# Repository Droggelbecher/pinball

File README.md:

Repository with code & electronics documentation for my personal pinball project.

This is far from a complete documentation that by itself woul be sufficient to replicate this project,
nevertheless it might be useful to some.

*boards* contains source code & notes on electronics for the various circuit boards used in the machine.
The main game logic is in the the control module which is basically a Raspberry Pi (plus some level-shifting electronics).
*common_software* contains some bits and pieces of code common to different modules,
mostly around inter-module communication (eg. checksum computation)

Checkout [http://leetless.de]() for more information.

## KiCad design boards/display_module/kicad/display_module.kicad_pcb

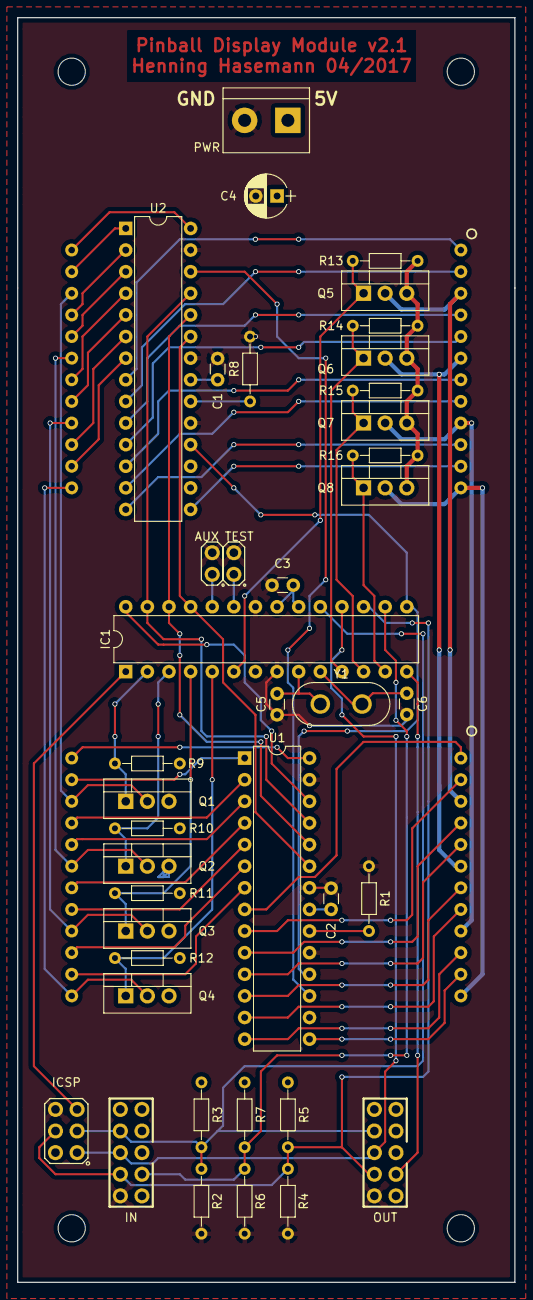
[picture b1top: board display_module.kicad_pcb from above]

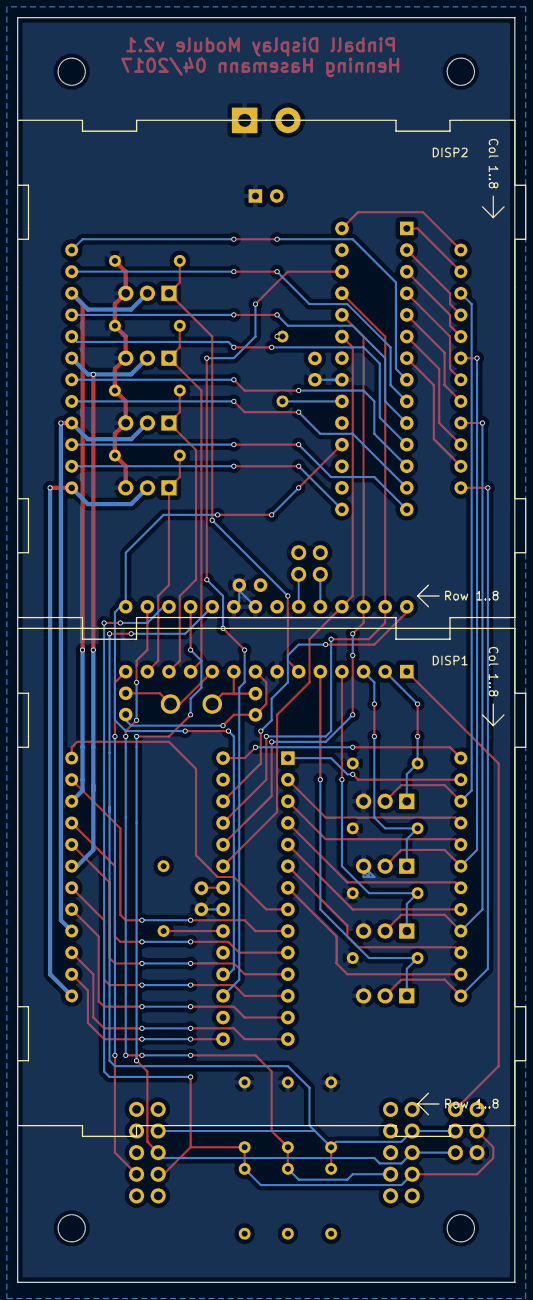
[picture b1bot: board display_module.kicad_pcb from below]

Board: 2 copper layers, 58.4 x 148.6 mm, 42 parts (2 on the bottom side), 68 nets.

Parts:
AUX: AUX; PINS1x2
C1, C2, C3: 100n; C_Disc_D3.0mm_W1.6mm_P2.50mm
C4: 10uF; CP_Radial_D5.0mm_P2.50mm
C5, C6: 22p; C_Disc_D3.0mm_W1.6mm_P2.50mm
DISP1, DISP2: LM23088A
IC1: ATMEGA328-P; DIP-28_W7.62mm
ICSP: ICSP; PINS3x2
IN: SW10
OUT: SW10
PWR: POWER; bornier2
Q1, Q2, Q3, Q4, Q5, Q6, Q7, Q8: NDP6020P; TO-220_Vertical
R1, R2, R4, R6, R8: 380; R_Axial_DIN0204_L3.6mm_D1.6mm_P7.62mm_Horizontal
R3, R5, R7: 190; R_Axial_DIN0204_L3.6mm_D1.6mm_P7.62mm_Horizontal
R9, R10, R11, R12, R13, R14, R15, R16: 10k; R_Axial_DIN0204_L3.6mm_D1.6mm_P7.62mm_Horizontal
TEST: TEST; PINS1x2
U1, U2: TLC5940NT; DIP-28_W7.62mm
Y1: 16M; Crystal_HC50_Vertical

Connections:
GND: AUX.2, C1.2, C2.2, C3.2, C4.2, C5.1, C6.2, IC1.8, IC1.22, ICSP.6, IN.5, OUT.5, PWR.2, R1.2, R2.2, R4.2, R6.2, R8.2, TEST.2, U1.19, U1.22, U1.27, U2.19, U2.22, U2.27
unnamed: C5.2, IC1.9, Y1.1
unnamed: C6.1, IC1.10, Y1.2
unnamed: DISP1.1, U1.8
unnamed: DISP1.2, U1.9
unnamed: DISP1.3, DISP2.3, Q5.2
unnamed: DISP1.4, U1.10
unnamed: DISP1.5, U1.11
unnamed: DISP1.6, DISP2.6, Q6.2
unnamed: DISP1.7, U1.12
unnamed: DISP1.8, U1.13
unnamed: DISP1.9, DISP2.9, Q7.2
unnamed: DISP1.10, U1.14
unnamed: DISP1.11, U1.15
unnamed: DISP1.12, DISP2.12, Q8.2
unnamed: DISP1.13, DISP2.13, Q4.2
unnamed: DISP1.14, U1.7
unnamed: DISP1.15, U1.6
unnamed: DISP1.16, DISP2.16, Q3.2
unnamed: DISP1.17, U1.5
unnamed: DISP1.18, U1.4
unnamed: DISP1.19, DISP2.19, Q2.2
unnamed: DISP1.20, U1.3
unnamed: DISP1.21, U1.2
unnamed: DISP1.22, DISP2.22, Q1.2
unnamed: DISP1.23, U1.1
unnamed: DISP1.24, U1.28
unnamed: DISP2.1, U2.8
unnamed: DISP2.2, U2.9
unnamed: DISP2.4, U2.10
unnamed: DISP2.5, U2.11
unnamed: DISP2.7, U2.12
unnamed: DISP2.8, U2.13
unnamed: DISP2.10, U2.14
unnamed: DISP2.11, U2.15
unnamed: DISP2.14, U2.7
unnamed: DISP2.15, U2.6
unnamed: DISP2.17, U2.5
unnamed: DISP2.18, U2.4
unnamed: DISP2.20, U2.3
unnamed: DISP2.21, U2.2
unnamed: DISP2.23, U2.1
unnamed: DISP2.24, U2.28
unnamed: IC1.1, ICSP.5
unnamed: IC1.2, Q1.1, R9.2
unnamed: IC1.3, Q2.1, R10.2
unnamed: IC1.4, Q3.1, R11.2
unnamed: IC1.5, Q4.1, R12.2
unnamed: IC1.6, Q5.1, R13.2
unnamed: IC1.11, Q6.1, R14.2
unnamed: IC1.12, Q7.1, R15.2
unnamed: IC1.13, Q8.1, R16.2
unnamed: IC1.14, OUT.7
unnamed: IC1.15, U1.18, U2.18
unnamed: IC1.16, IN.7, R6.1, R7.1
unnamed: IC1.17, ICSP.4, IN.4, OUT.4, R4.1, R5.1
unnamed: IC1.18, ICSP.1, IN.3, OUT.3
unnamed: IC1.19, ICSP.3, IN.2, OUT.2, R2.1, R3.1
unnamed: IC1.23, TEST.1
unnamed: AUX.1, IC1.24
unnamed: IC1.25, U1.23, U2.23
unnamed: IC1.26, U1.24, U2.24
unnamed: IC1.27, U1.25, U2.25
unnamed: IC1.28, U1.26
unnamed: R1.1, U1.20
unnamed: R8.1, U2.20
unnamed: U1.17, U2.26
VCC: C1.1, C2.1, C3.1, C4.1, IC1.7, IC1.20, IC1.21, ICSP.2, PWR.1, Q1.3, Q2.3, Q3.3, Q4.3, Q5.3, Q6.3, Q7.3, Q8.3, R3.2, R5.2, R7.2, R9.1, R10.1, R11.1, R12.1, R13.1, R14.1, R15.1, R16.1, U1.21, U2.21

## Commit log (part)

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2014-09-18 Started display board instructions
2014-09-21 saved some data sheets
2014-09-30 started building control module software from spi test code
2014-10-01 Display functions for cont module, forgotten files from display module.
2014-10-01 forgotten checkins
2014-10-01 gitignore
2014-10-01 some playing around with the gradient function
2014-10-02 Continued display module soldering instructions
2014-10-03 More work on display module
2015-01-24 added led matrix spec
2015-01-24 somewhat more useful display debug rendering mode
2015-01-28 some debugging (trying to get spi com working for multiple displays)
2015-02-01 Experimenting with 2 disp modules, currently SS forwarding doesnt work yet.
2015-02-01 Minor fixes, first successful multi-display run!
2015-02-09 some trying around with SS interrupt, doesnt seem to work
2015-02-10 added tracer module for arduino
2015-02-10 display colors now palette based
2015-02-10 some tweaking on display ISR, SPI transmission speed, framerate
2015-02-10 more stable FPS control
2015-02-10 started PCF font reader code
2015-02-16 wip: PCF font rendering
2015-02-16 wip: pcf
2015-02-26 Debug SPI/GPIO/display impls for testing on pc.
2015-03-07 added some (publicy available) fish tales pinball documents for reference
2015-03-22 added solenoid driver code
2015-03-23 turns out we dont need no delay between power and hold but an elco instead ;)
2015-04-18 switches module
2015-04-18 playfield svg
2015-04-19 work on switches module, bugfixing on controller module
2015-04-26 line debugger
2015-05-09 successful test of switches module via SPI @4kHz
2015-05-13 first somewhat working flipper control (there still seem to be some bit flips due to SPI transmission errors)
2015-05-14 crc8 checksums for SPI comm with solenoid board
2015-05-15 solenoid driver now defaults to all solenoids off
2015-05-16 initial drop target bank support
2015-05-17 renaming "buttons" to "switches"
2015-05-17 makefile fix for easier local pc compilation
2015-05-17 debug display now uses ascii art-ish chars instead of numbers
2015-05-17 scrolling pcf font on (debug) display :-)
2015-05-17 checksum use for comm with switches module
2015-05-17 bugfix: endianness error in pcf.c
2015-05-17 control module defaults to all switches open
2015-05-20 Some testing/debugging of drop target bank 0.
2015-05-23 preliminary audio support using openal
2015-05-25 hopefully somewhat more useful audio api
2015-05-31 provided scripts so raspberry can fetch and compile most recent software version automatically
2015-05-31 added some background tracks
2015-05-31 deployment, fixed memory bug in pcf reader
2015-06-02 somewhat more useful check_compile.sh script
2015-06-03 wip: streaming audio, current problem: dynamic vector for playlist?!
2015-06-04 normalized audio tracks
2015-06-14 wip: display module
2015-06-14 debugging of display modules/fps
2015-07-04 more solenoid ports
2015-07-16 successfully tested lamp driver via SPI
2015-08-14 wip: switching to c++14
2015-08-30 wip: porting to c++
2016-01-30 started porting pcffont
2016-01-30 pcf.cc
2016-01-30 basic game logic seems to be compilable again on raspberry
2016-01-31 flippers functional again
2016-01-31 beautification, slingshot control
2016-03-20 spi comm bugfix, enabled slingshot solenoids
2016-03-20 converted audio module to c++
2016-03-20 squash-merged pcf port branch, added framer
2016-03-20 WIP: solenoids += bumpers
2016-03-25 coordinate
2016-03-25 added pcf test
2016-03-25 Switched to cmake (tested: MacOSX)
2016-03-25 fixed .gitignore
2016-03-25 compilable
2016-03-25 moved canvas modules into their own subdir
2016-03-25 started work on curses display
2016-03-25 first (random) paintings on curses display
2016-03-26 pcf_font.cc compilable
2016-03-26 pcf renders font on curses display
2016-03-26 coordinate/scrolling canvas
2016-03-28 little fixes
2016-03-28 scrolling now works in both dimensions
2016-03-28 moved all display stuff to display/, more appropriate colors in curses display
2016-03-29 broadcast canvas
2016-04-03 mode compile on archlinux
2016-04-16 added kicad files for new WIP display module
2016-05-27 kicad update
2016-05-28 compiles and runs on raspi
2016-05-28 nicer switch state display
2016-05-28 print all switch states
2016-05-28 death star hole
2016-05-29 death star explode sound
2016-05-29 audio volume adjust
2016-05-30 ball return, more sounds, solenoid driver rewrite
2017-01-22 WIP: Changing display module to use TLC5940
2017-01-22 WIP: compiles for now, but still TODOS open (do not try to run this as is!)
2017-02-26 match pins to breadboard
2017-03-08 display timing fixes
2017-03-08 additional SCLK cycle at the end of grayscale input
2017-03-08 fixed row/column indexing mixup
2017-03-09 re-enabled interrupts, slightly more efficient interrupt flag reset
2017-03-11 spi connector pin notes
2017-03-13 more display fixes
2017-03-13 kicad work
2017-03-14 control module: game logic += delayed ball return
2017-03-14 display module design
2017-03-14 refactoring: combine interfaces (switches, solenoids, display,...) into one to allow for curses-based super-control panel
2017-03-14 more work on curses interface
2017-03-14 fixed solenoid reset bug
2017-03-15 use "foreach" for key table iteration
2017-03-15 mach timer fix and more complete curses interface
2017-03-18 finished display module layout, sent to printing
2017-03-18 fix compilation on archlinux, remove CLOCK_REALTIME dependency
2017-04-07 WIP: Refactoring curses interface
2017-04-07 WIP: display module PCB design v2.1
2017-04-08 display module fixes during hw test
2017-04-09 curses interface refactored, SPI part still TODO
2017-04-09 WIP: refactoring SPI game interface to new structure
2017-04-10 SPI interface compiles again on archlinux (TODO: test running on raspi)
2017-04-10 Display Module PCB v2.1
2017-05-11 Fix test jumper read in disp module
2017-07-04 allow to set AVRDUDE_BAUDRATE on cammandline for display module
2017-11-04 display/frame rate control improvements
2017-11-25 Scrolling now FPS independent, framer improvements
2017-11-25 Minimal README.md
2018-02-23 default to program via ArduinoISP
2018-03-25 solenoid driver field fixes
2018-03-26 CMakelist for 2.8, curses now optional
2018-03-26 Removed redundant defines from config.h (see linux_spi.h)
2018-03-26 Fix framer int overflow issue
2018-03-26 Added Death Star hole button to curses iface
2018-03-26 Left flipper now cycles through lamps
2018-03-26 KeepValueDelay doesnt need framer ref
2018-03-26 Dummy/Curses/SPI interface construction cleanup
2018-03-26 Added set(bool) method to actuators
2018-03-26 state buffer now guarenteed to compare states from different frames
2018-03-26 deploy script +x
2018-03-27 selftest for lamp driver
2018-03-27 Make OpenAL-based audio optional (alternative is mock audio)
2018-03-27 Minor fixes
2018-03-27 enable profiling w/ gprof
2018-03-27 Converted to positive logic (1=true="on" everywhere but inside SPI driver)
2018-03-27 Profiling & Assertions configurable via CMake conf
2018-03-27 Fixed DTB0 switch contact order
2018-03-27 Performance improvements in canvas & pcf font
2018-03-28 Added interval stats to report FPS also in "headless" mode for debugging
2018-05-10 Logging & Debugging implementations for curses UI.
    * Logging in curses UI
    * Curses UI can directly control solenoids
    * Code cleanup & small fixes
    Squashed commit of branch 'logging'.
    Squashed commit of the following:
    commit 5552ae0e7d4a564bff2df1e2854d3a2d8fd5ec7e
2018-05-12 WIP: restructuring canvas/pcf, adding unittests
2018-05-13 scrolling canvas
2018-05-17 WIP: pre-vacation commit
2018-06-16 CMakelists restructuring, font reader into seperate directory
2018-10-27 WIP: Refactoring & new font rendering process
2018-10-27 Fixed font-blitting crash, still WIP
2018-10-28 Added missing pcf_font.h
2018-10-28 scrolling fixes
2018-11-17 Fixed more scrolling issues
2018-11-17 Original soundtrack (not in repo for legal reasons, sorry)
2018-11-18 Porting some things to D just for fun...
2018-11-18 Make font_reader generate D code
2018-12-26 font blitting
2018-12-26 display clearing
2018-12-27 Text scrolling
2018-12-27 Make blitting @nogc
2018-12-27 More font/scrolling goodness
2018-12-27 Some frame-rate regulation
2018-12-27 switches & solenoids frame_start
2018-12-28 code beautification: font closure as lambda
2018-12-29 Colored fonts & simpler string blitting
2019-01-01 Fine-tuning intro and ball return / keep value delay
2019-01-12 Added OpenAL audio
2019-01-13 Curses Interface: sw/sol states & logging
2019-01-27 bcm2708 SPI
2019-01-28 bcm2708 transfer_and_check & log format typo
2019-02-08 Buffer Logger & Log framerate
2019-02-08 Score display
2019-02-08 Flash fuses & minor fixes
2019-02-08 Driver s/w for target light LEDs
2019-02-08 More readable ordering of switches enum
2019-02-08 Fixed logging
2019-02-08 counting-up score display
2019-02-08 Refactor game logic aspects into mixins
2019-02-08 Scoring sound
2019-02-09 Raspi fixes & clean quitting
2019-02-09 WIP: Stuttering audio on Raspberry
2019-02-10 WIP: sound fixing
2019-02-24 Audio: Checking out libmad on plain OpenAL
2019-03-09 WIP Audio debugging: Correct alBufferData corrrectly plays sine tone
2019-03-09 WIP Audio debugging: Mono rocket sound working
2019-03-09 Audio can play music & sound in parallel
2019-03-09 Implemented playlist for MAD&OpenAL
2019-03-10 MultiSound & further audio fixes
2019-03-17 LED stripe driver start
2019-03-24 LED stripe driver fist successful test
2019-03-24 implemented some led strip coloring commands
2019-03-24 SPI transfer (untested)
2019-03-29 refactor: use IDs to recognize new commands
2019-03-30 Unified color-setting & animation into one command
2019-03-30 LED stripe actuator, minor compilation fixes for raspi
2019-03-31 Improve logging, make code profilable (WIP)
2019-03-31 WIP: Audio decoding performance issues
2019-03-31 Fixed audio performance by moving from SWIG to DSTEP bindings.
2019-03-31 Removed unneeded C++ sources
2019-03-31 re-enabled score sound, minor fixes
2019-03-31 Further audio problems (mmap commit error) fixed by moving from OpenAL Soft to SDL
2019-04-06 WIP: Game-logic: mixins to classes
2019-04-06 Scheduler: Tasks new have a priority
2019-04-06 Game logic aspects now more decoupled as classes instead of mixins
2019-04-07 Game logic: Use LED actuator, score display
2019-04-10 First raspi->LED comm, but we dont do checksums yet?!
2019-04-11 fix bit actuator to work on byte-level
2019-04-12 some source cleanup
2019-04-13 led stripe selftest mode
2019-04-13 lamps
2019-04-14 WIP in the field fixes
2019-04-14 Field fixes: Ball return rerouted
2019-04-14 gome logic refactor and untested SPI disp control
2019-04-19 .nvimrc -> .projections.json, more flexible
2019-04-20 projections -> .lvimrc
2019-04-20 Removed ole src/ dir
2019-04-20 Death star PNG animation :-)
2019-05-03 Story: start with intro again
2019-09-02 cmakelists not needed for d version
2019-09-24 Added display test, removed further PNG deps
2019-09-24 display module timing fixes (flicker)
2019-09-24 fix(display): SPI recv timeout too narrow
2019-09-24 display colors improvement and mirrord
2019-09-25 fix(control): Bumper switcharoo & play field resetting
2019-09-26 Reaction to death star hole entry
2019-09-26 Extend LED actuator to also take over lamp control
2019-09-26 feat(control): Lamp control in curses interface
2019-09-26 feat(control): Use lamps in some interactions
2019-09-27 feat(control): Spinner preparations
2020-03-14 10k score now achievable
2020-04-04 String sprites incl. Leia & death star advance
2020-08-18 remove resource directory from repo completely
2020-12-25 Some minor story updates
2021-11-11 Code cleanup, some highscore work
2021-11-11 fix some highscore issues
2021-11-11 mising file
2021-11-19 Code cleanup and port corrections
2022-01-22 extend led module banks, use led stripe more
2022-01-22 more lighting logic
2023-09-24 Pin ncurses, fixe sharedLog for newer DMDs
2023-09-27 Allow disabling audio via CLI
2023-09-28 Made highscore system more robust against file corruption
2023-09-28 Fixed accidental 1000 points in mock mode
2023-09-28 Possibly fixed score entry issues
2023-09-28 More forgiving highscore prompt, allow correction of earlier chars
2023-10-20 minor
